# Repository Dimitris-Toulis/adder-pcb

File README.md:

# Adder + Capacitors charge PCB

This is a pcb with two parts:
1) A half-adder operated with two push buttons
2) A demo of the effect of resistance in the charge time of capacitors

## BOM
- 2 Battery holders
- 2 10uF Capacitors
- 6 5mm LEDs
- 12 NPN transistors
- 6 220Ω Resistors
- 8 4.7kΩ Resistors
- 5 47kΩ Resistors
- 3 Push buttons

Made for [Hackclub's Solder YSWS](https://solder.hackclub.com/) by `@Dimitris` on Slack!

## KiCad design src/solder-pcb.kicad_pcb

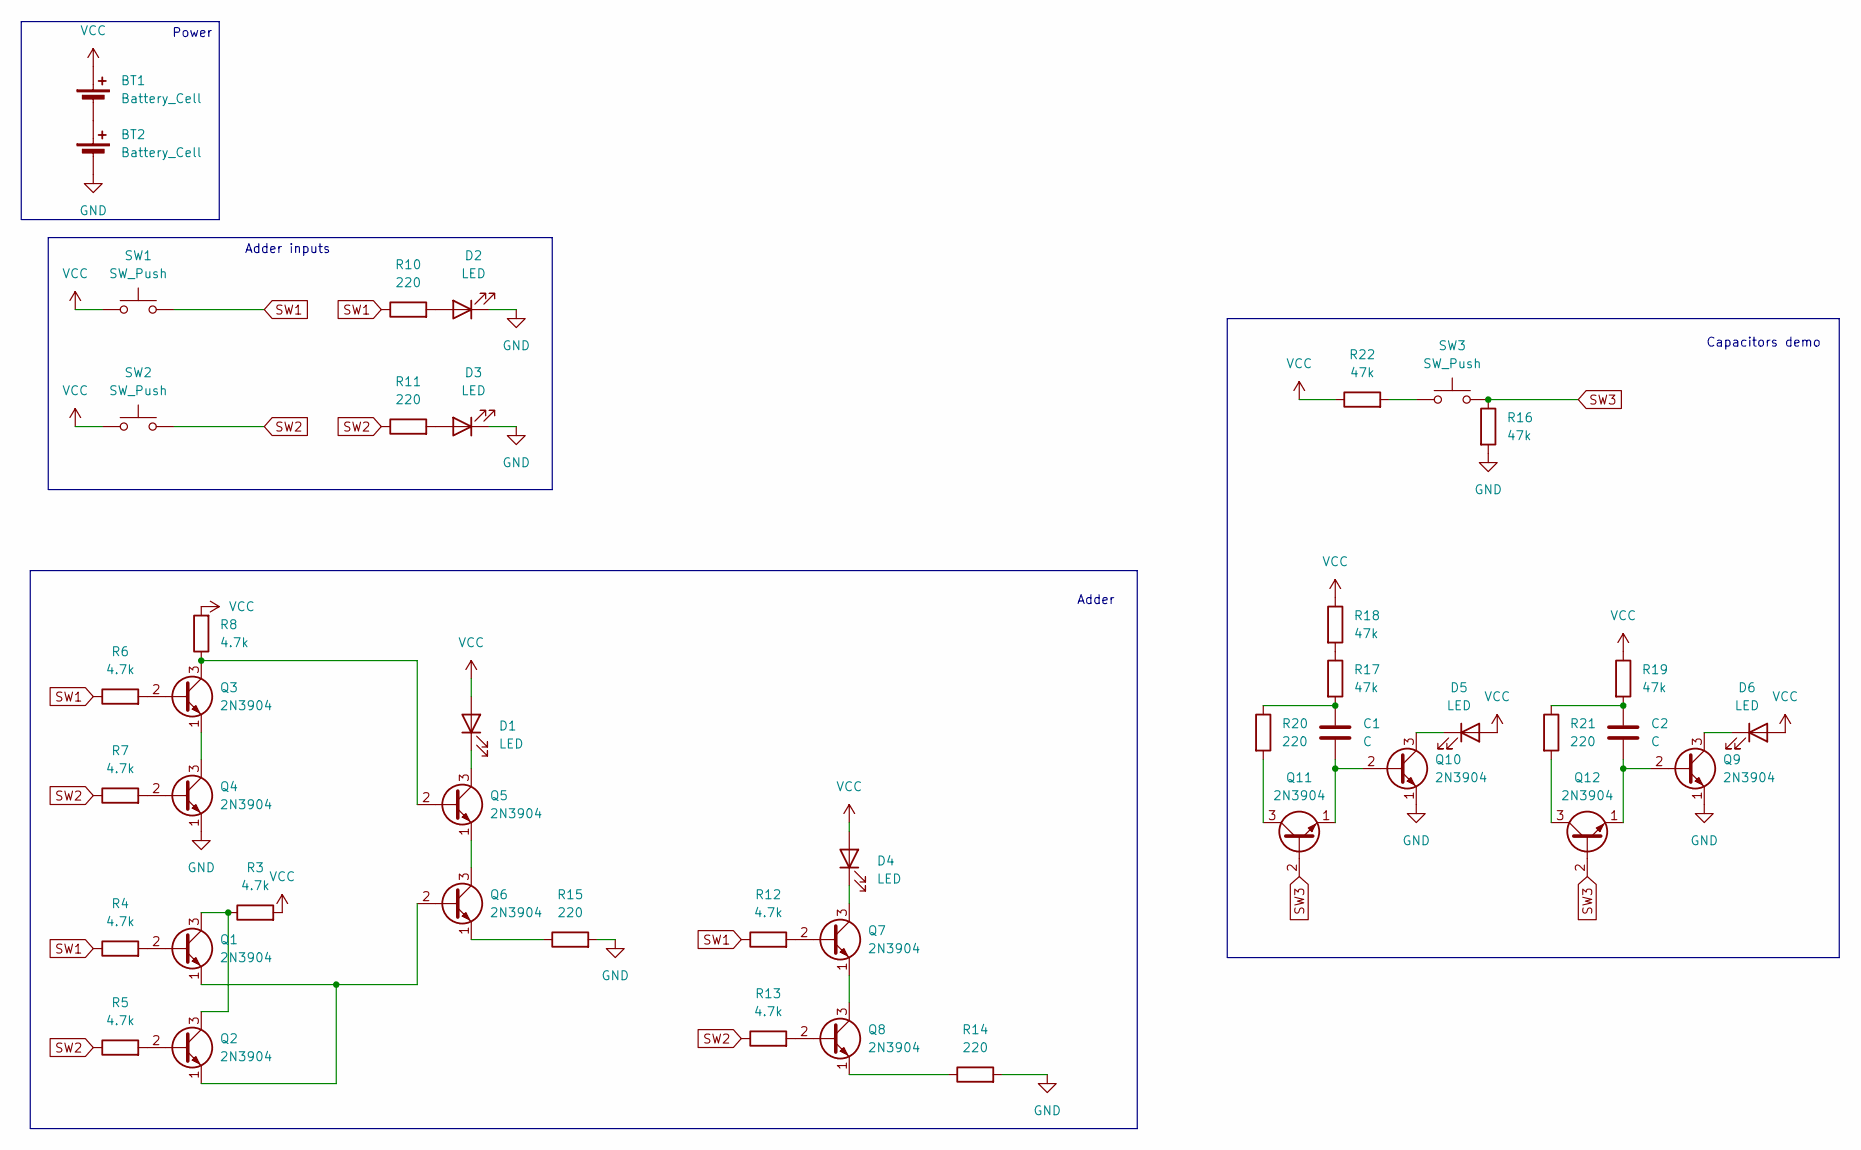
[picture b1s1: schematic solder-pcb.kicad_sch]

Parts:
BT1, BT2: Battery_Cell; BatteryHolder_Keystone_3034_1x20mm
C1, C2: C; CP_Radial_D8.0mm_P5.00mm
D1, D2, D3, D4, D5, D6: LED; LED_D5.0mm
Q1, Q2, Q3, Q4, Q5, Q6, Q7, Q8, Q9, Q10, Q11, Q12: 2N3904; TO-92L_HandSolder
R3, R4, R5, R6, R7, R8, R12, R13: 4.7k; R_Axial_DIN0207_L6.3mm_D2.5mm_P7.62mm_Horizontal
R10, R11, R14, R15, R20, R21: 220; R_Axial_DIN0207_L6.3mm_D2.5mm_P7.62mm_Horizontal
R16, R17, R18, R19, R22: 47k; R_Axial_DIN0207_L6.3mm_D2.5mm_P7.62mm_Horizontal
SW1, SW2, SW3: SW_Push; SW_PUSH_6mm

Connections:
GND: BT2.2 (-), D2.1 (K), D3.1 (K), Q4.1 (E), Q9.1 (E), Q10.1 (E), R14.2, R15.2, R16.2
unnamed: BT1.2 (-), BT2.1 (+)
unnamed: C1.1, R17.2, R20.1
unnamed: C2.1, R19.2, R21.1
unnamed: D1.1 (K), Q5.3 (C)
unnamed: D2.2 (A), R10.2
unnamed: D3.2 (A), R11.2
unnamed: D4.1 (K), Q7.3 (C)
unnamed: D5.1 (K), Q10.3 (C)
unnamed: D6.1 (K), Q9.3 (C)
unnamed: Q1.2 (B), R4.2
unnamed: Q1.3 (C), Q2.3 (C), R3.1
unnamed: Q1.1 (E), Q2.1 (E), Q6.2 (B)
unnamed: Q2.2 (B), R5.2
unnamed: Q3.2 (B), R6.2
unnamed: Q3.3 (C), Q5.2 (B), R8.1
unnamed: Q3.1 (E), Q4.3 (C)
unnamed: Q4.2 (B), R7.2
unnamed: Q5.1 (E), Q6.3 (C)
unnamed: Q6.1 (E), R15.1
unnamed: Q7.2 (B), R12.2
unnamed: Q7.1 (E), Q8.3 (C)
unnamed: Q8.2 (B), R13.2
unnamed: Q8.1 (E), R14.1
unnamed: C1.2, Q10.2 (B), Q11.1 (E)
unnamed: Q11.3 (C), R20.2
unnamed: Q12.3 (C), R21.2
unnamed: C2.2, Q9.2 (B), Q12.1 (E)
unnamed: R17.1, R18.2
unnamed: R22.2, SW3.1
SW1: R4.1, R6.1, R10.1, R12.1, SW1.2
SW2: R5.1, R7.1, R11.1, R13.1, SW2.2
SW3: Q11.2 (B), Q12.2 (B), R16.1, SW3.2
VCC: BT1.1 (+), D1.2 (A), D4.2 (A), D5.2 (A), D6.2 (A), R3.2, R8.2, R18.1, R19.1, R22.1, SW1.1, SW2.1

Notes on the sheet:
Capacitors demo
Adder
Power
Adder inputs

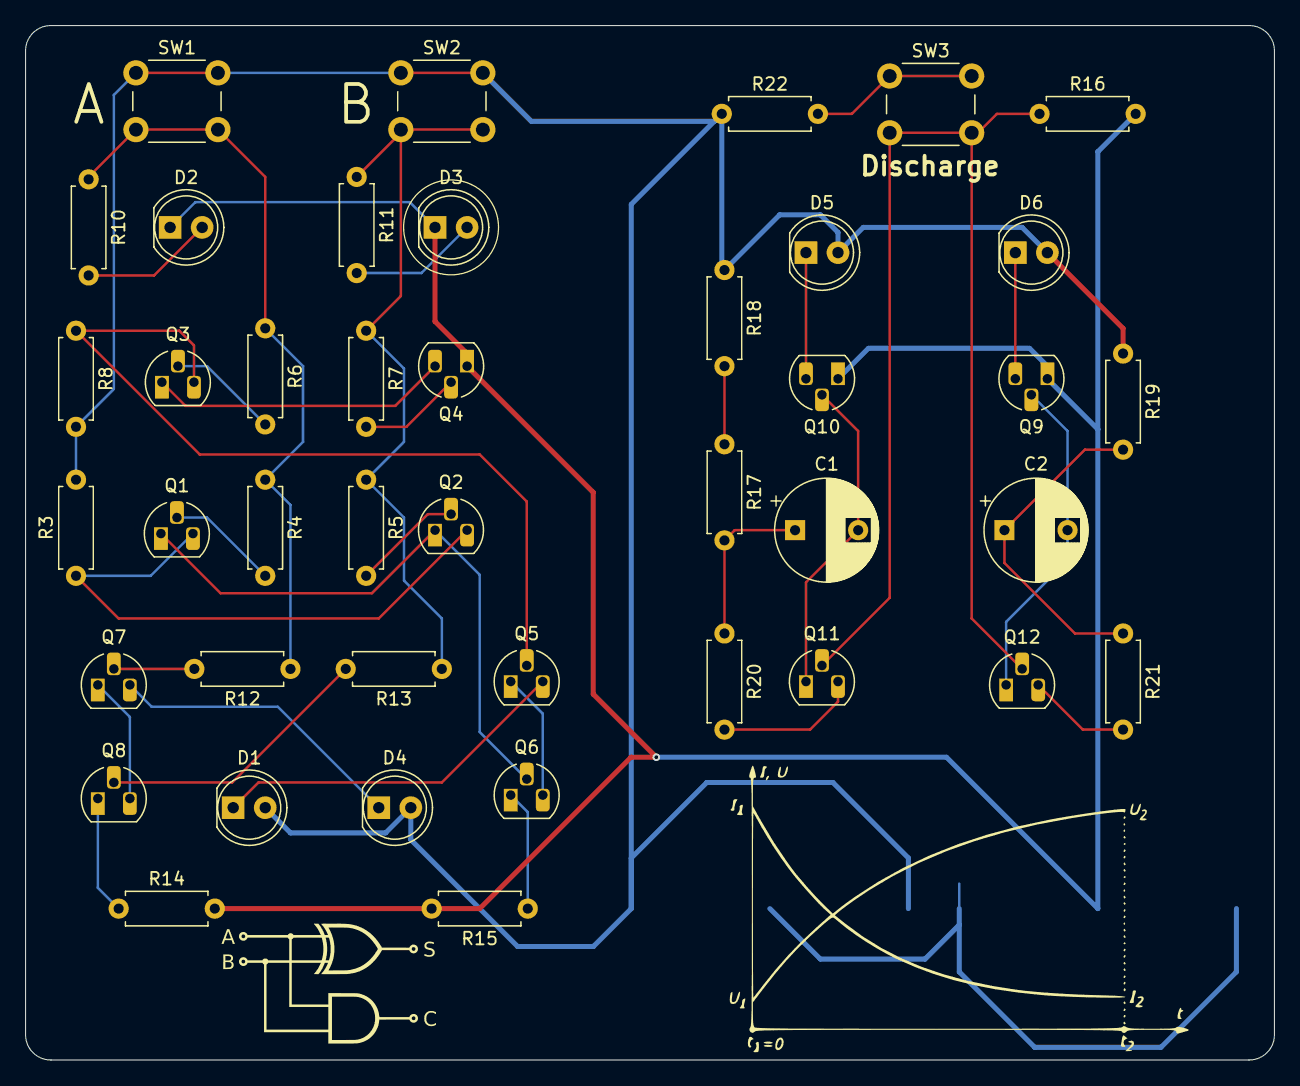
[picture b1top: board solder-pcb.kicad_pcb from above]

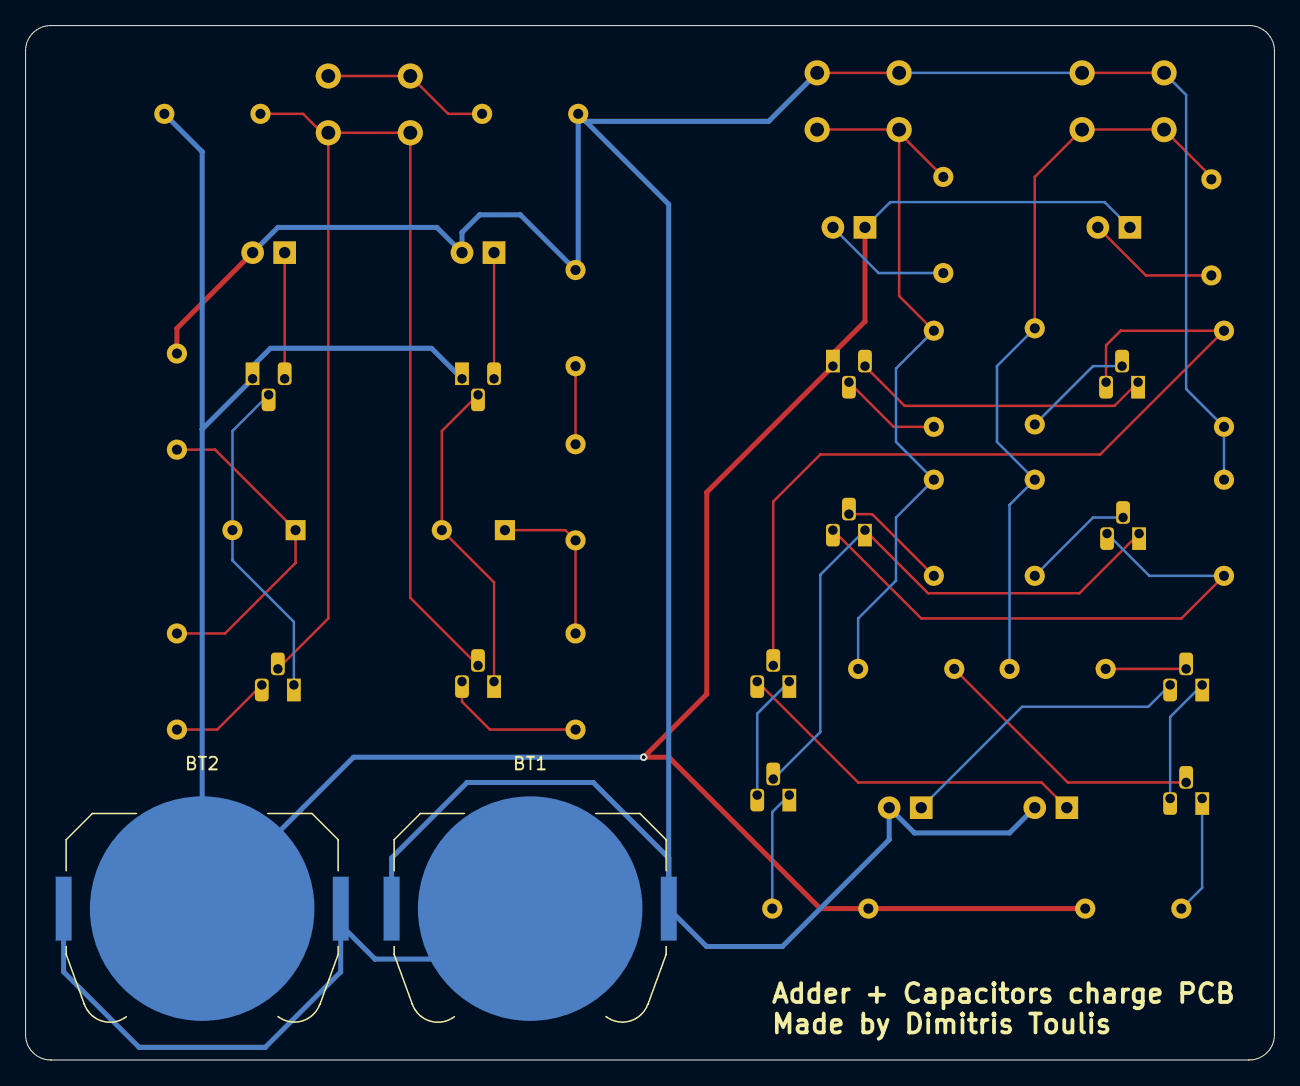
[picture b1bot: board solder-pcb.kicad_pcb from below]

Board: 2 copper layers, 99.0 x 82.0 mm, 44 parts (2 on the bottom side), 34 nets.

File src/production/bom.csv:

Designator,Footprint,Quantity,Value,LCSC Part #
"BT1, BT2",BatteryHolder_Keystone_3034_1x20mm,2,Battery_Cell,
"C1, C2",CP_Radial_D8.0mm_P5.00mm,2,C,
"D1, D2, D3, D4, D5, D6",LED_D5.0mm,6,LED,
"Q1, Q10, Q11, Q12, Q2, Q3, Q4, Q5, Q6, Q7, Q8, Q9",TO-92L_HandSolder,12,2N3904,
"R10, R11, R14, R15, R20, R21",R_Axial_DIN0207_L6.3mm_D2.5mm_P7.62mm_Horizontal,6,220,
"R12, R13, R3, R4, R5, R6, R7, R8",R_Axial_DIN0207_L6.3mm_D2.5mm_P7.62mm_Horizontal,8,4.7k,
"R16, R17, R18, R19, R22",R_Axial_DIN0207_L6.3mm_D2.5mm_P7.62mm_Horizontal,5,47k,
"SW1, SW2, SW3",SW_PUSH_6mm,3,SW_Push,

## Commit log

2025-05-24 Add production files
2025-05-25 Add some silkscreen diagrams
